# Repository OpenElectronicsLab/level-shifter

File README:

Converts 5v to 3.3v

The single-sided PCB design is simple enough that it can be etched at home.

Uses two Texas Instruments: SN74LS126ANE4

Buffers & Line Drivers Quad Bus Buffer With 3-State Outputs

http://nl.mouser.com/ProductDetail/Texas-Instruments/SN74LS126ANE4/?qs=sGAEpiMZZMutXGli8Ay4kP28D9wZ8SQIMqpIftnsrsk%3d

License
-------
Copyright (C) 2012-2021 Medlock, Herman, and Shaw
CERN Open Hardware Licence v1.2

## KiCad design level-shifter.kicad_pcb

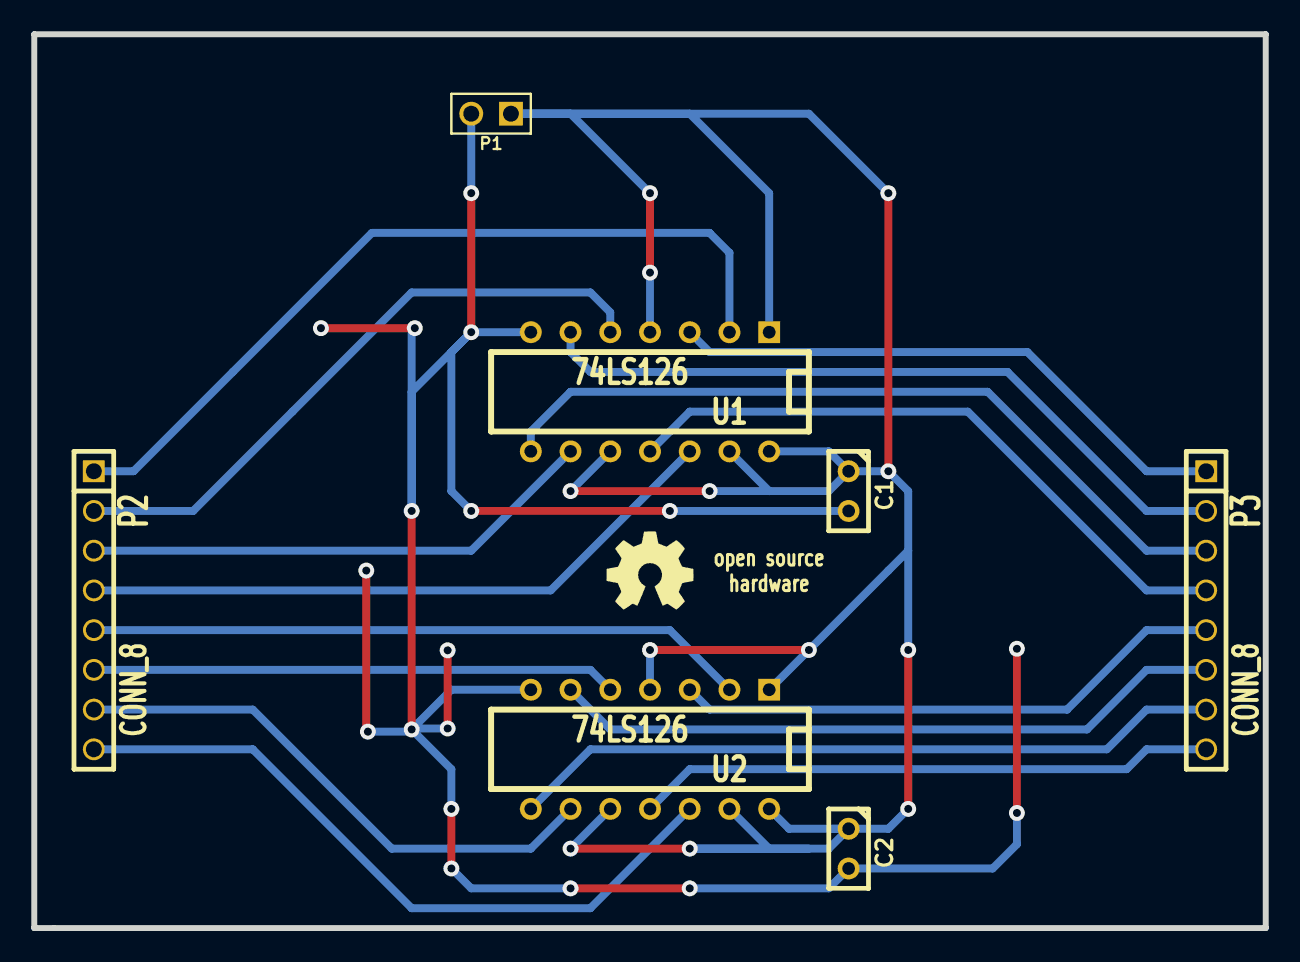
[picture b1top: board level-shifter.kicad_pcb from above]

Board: 2 copper layers, 78.7 x 57.1 mm, 7 parts (0 on the bottom side), 18 nets.

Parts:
C1, C2: 1uF; C1
P1: CONN_2; PIN_ARRAY_2X1
P2, P3: CONN_8; PIN_ARRAY_8x1
U1, U2: 74LS126; DIP-14__300

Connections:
GND: C1.2, C2.2, P1.2, U1.7, U2.7
unnamed: P2.1, U1.2
unnamed: P2.2, U1.5
unnamed: P2.3, U1.9
unnamed: P2.4, U1.12
unnamed: P2.5, U2.2
unnamed: P2.6, U2.5
unnamed: P2.7, U2.9
unnamed: P2.8, U2.12
unnamed: P3.1, U1.3
unnamed: P3.2, U1.6
unnamed: P3.3, U1.8
unnamed: P3.4, U1.11
unnamed: P3.5, U2.3
unnamed: P3.6, U2.6
unnamed: P3.7, U2.8
unnamed: P3.8, U2.11
VCC: C1.1, C2.1, P1.1, U1.1, U1.4, U1.10, U1.13, U1.14, U2.1, U2.4, U2.10, U2.13, U2.14

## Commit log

2012-01-21 init
2012-01-21 initial wires connected
2012-01-21 change 3.3 to VCC to satisfy rules check
2012-01-21 gitignore
2012-01-21 add a .brd file
2012-01-21 playing with routing the tracks
2012-01-22 design rules check now passes
2012-01-29 create an 8x1 connector module
    the SIL-8x1 has 0.032 inch holes drilled,
    this new PIN_ARRAY has 0.0400 inch holes
2012-01-29 switch from using SIL to PIN_ARRAY
    changes drilled holes to larger size.
2012-01-29 add OSHW logo
2012-01-29 add GND zone for less etching
2012-02-19 added a README
2013-08-25 add more ground zones
2015-12-05 add the *-cache.lib files for forward compatibility
2021-02-23 Create LICENSE.txt
    must not have added one earlier - copied from another project of similar vintage
2021-02-26 kicad update to 5.1
2021-02-26 remove obsolete files after update
2021-02-26 README: add license note
